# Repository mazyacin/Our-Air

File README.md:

<div align="center">
  
</div>
<div align="center">

</div>

<h1 align="center">Our-Air</h1>

<h2 align ="center">A platform for Our Environment:</h2> 

التلميذ : **مزوز أحمد الامين** 

**مسابقة الابتكار المدرسي الطبعة 2 الانظمة الذكية و انترنت الاشياء**

**هذا المشروع مفتوح المصدر تحت رخصة GNU  و هذه الجيت هاب ريبو نسخة احتياطية في حالة تلف ملفات المسابقة المرفقة** 
<h1 align="center"> 
The Problem :
</h1>

<h4 align="center"> With the overall all change with Our environment  we notice an increasing in Disasters like Air Pollution ,Wildfires
Water Pollution, Big Chemical Accidents, and environmental emergencies , but we only act when they happen , what if we 
had something , that lets us do advanced research and predicting</h4>

**Our-Air** Is a complete environmental scanning network that with the **flagship best in the world** sensors that scan for :

**Nitrogen Oxides(NOX)** : A group of very important gases because they are the same gases that cars and Factories emit 

**Volatile Organic Compounds (VOCs)** : A group of gases that is emitted from Paint, Oil Refineries, and Factories in general

**Humidity** : The consternation of vapor water in the Air , it is the Reason for Mold, and important for Respiratory Comfort 

**Temperature** : It tells us the thermal state of our environment, main reason of heatstroke

**Barometric Pressure** : It tells us the weight of the atmosphere, can be used to predict storms/rain

**Carbon Dioxide** : True sensing of the Co2 that`s  in the air we breath

**RunTime** : Nodes Up to 1.2 years of run time on 2x18650 in a parallel configuration, and Master around 87h of runtime on its backup battery 
with automatic Power Switching

---

And Our-Air has a **Desktop App** made to analyze the data both live and in a **sqlite db** format with **advanced environment researching tools** such as SQL query code field and professional graphs with a sleek design

<div align="center">

</div>

---
<h1 align="center"> 
But Why Our-Air : 
</h1>

-1 Its **fully open source**  , This project does`nt have to stop its development   

-2 The sensors all have 2 common reading and those are the humidity and temperature, and this lets us compare sensor data to detect faulty sensors 

-3 Community driven nodes that the  **smart** system adds to its **network**  

-4 Achieving **Long Range** without a Lora IC, our system uses a broadcasting esp-now interface with range up to 1.5km 

-5 No encryption to the sent packets  and broadcast mode, this lets solo researchers and tech hobbyists check their local environment data , even build their own project around the sensor data

-6 Very versatile the system is dynamic so it can read multiple kinds of data , For example someone can make one that watches water level at a nearby lake,

Or someone can make a bracelet with a button to notify the nearby receiver when that the person wearing the bracelet is lost, 

<h1 align="center"> 
Our-Air Node technical details 
</h1>

<h2 align="center"> 
Schematic : 
</h2>

<div align="center">
  
</div>

<h1 align="center"> 
Rough Bom : 
</h1>

 **Microcontroller : Esp32 C3 U1 N4 , Risc-V 160Mhz , 4MB of flash memory** 

<h2 align="center"> 
Sensors: 
</h2>

   | Sensor| Manufacturer | Description |
| --- | --- | --- |
| Bme690 | Bosch | The bme690 is Bosch latest environment sensor , and is the worlds best general environmental sensor , it is set to Spi Mode |
| SGP41| Senisiron|one of Senisiron`s latest Sensors whats special about it is its NOX sensing|
| SCD41| Senisiron|one of the Only sensors in the World , that can truly sense CO2 in the Air| 

<h2 align="center"> 
ICs: 
</h2>

   | Ic| Manufacturer | Description |
| --- | --- | --- |
| IP2312 | Injoinic | a high end charging ic set to 3A charging, whats special about it is the buck based design allowing low heat under full load |
| TPS63802| Texas instruments  |a high efficiency Buck and Boost ic with a Input voltage of 1.2v to 5.5v and Output of 3.3v , its efficiency is 95% , at full load it reaches 45°C which prevents burnouts, and its design lets use an 18650 directly , in the pcb its  used to power the components|
| CK340k| WCH |its a USB to UART programmer, in this case its used to flash the code to the MCU , and view live data , also offering debugging for both Nodes and Master| 

<div align="center">
  
</div>
<h2 align="center"> 
Pcb Specs :
</h2>

 **4 Layer Design** : a 4 layer based pcb design lets us minimize Emi Noise , Improve Stability and Reliability
 
 **TearDrops** : they Improve Reliability on the Long Run , its a must for a pcb like this that runs for long sessions
 
 **Smart heat accommodated design** : the Sensors are sensitive to heat so i designed it for thermal isolation 
 
 **Stitching Vias** : they were used to lower noise and help with heating 

 **fencing Vias** : they are used to make sure the LongRange Stays stable
 
 **External Antenna** : there is a IPX connector to connect an external Antenna

<div align="center">
  
</div>
<h1 align="center"> 
Casing Design : 
</h1>

  <h2 align="center"> 
Features : 
</h2>

   **OuterWalls** : ~125mm x 98mm 
      
   **InnerWalls** : ~120mm x 95mm
     
  **Wall Thickness** : 3mm
      
   **Closing Mechanism** : Annular snap-fit with 2mm long lip and 2 vertical cuts  for easier use when closing or opening
      
   **Meterial** : 9600 White Resin
      
   **Breathing Vents** : needed so the sensors can read the measurement of outside air
   
   **Ports** : there are spaces for the 2 USB C receptacles (35mm x ~4mm)and the external antenna(~7mm x ~15mm)

   <h1 align="center"> 
Our-Air Master technical details 
</h1>

<h2 align="center"> 
Schematic : 
</h2>

<div align="center">
  
</div>

<h1 align="center"> 
Rough Bom : 
</h1>

 **Microcontroller : Esp32 C3 U1 N4 , Risc-V 160Mhz , 4MB of flash memory** 
 **SD Card (8gb)

ICs: 
</h2>

   | Ic| Manufacturer | Description |
| --- | --- | --- |
| IP2312 | Injoinic | a high end charging ic set to 3A charging, whats special about it is the buck based design allowing low heat under full load |
| TPS63802| Texas instruments  |a high efficiency Buck and Boost ic with a Input voltage of 1.2v to 5.5v and Output of 3.3v , its efficiency is 95% , at full load it reaches 45°C which prevents burnouts, and its design lets use an 18650 directly , in the pcb its  used to power the components|
| CK340k| WCH |its a USB to UART programmer, in this case its used to flash the code to the MCU , and view live data , also offering debugging for both Nodes and Master| 
| DS3231SN| Maxim Integrated |A RTC Ic (Real Time Clock ic ) used to make the timestamps of the when Sensors is received by the Master  | 
<div align="center">
  
</div>
<h2 align="center"> 
Pcb Specs :
</h2>

 **4 Layer Design** : a 4 layer based pcb design lets us minimize Emi Noise , Improve Stability and Reliability
 
 **TearDrops** : they Improve Reliability on the Long Run , its a must for a pcb like this that runs for long sessions
 
 **Stitching Vias** : they were used to lower noise and help with heating 

 **fencing Vias** : they are used to make sure the LongRange Stays stable
 
 **External Antenna** : there is a IPX connector to connect an external Antenna

<div align="center">
  
</div>
<h1 align="center"> 
Casing Design : 
</h1>

  <h2 align="center"> 
Features : 
</h2>

   **OuterWalls** : ~168mm x 107mm 
      
   **InnerWalls** : ~160mm x 100mm
     
  **Wall Thickness** : 3mm
      
   **Closing Mechanism** : Annular snap-fit with 2mm long lip and 2 vertical cuts  for easier use when closing or opening
      
   **Meterial** : 9600 White Resin
   
   **Ports** : there are spaces for the 2 USB C receptacles (35mm x ~4mm)and the external antenna(~7mm x ~15mm) and Sd card ( ~60mm x 16mm) the holes for the sd card and external antenna are merged

<h1 align="center">
Node Logic  :
</h1>

<h3 >
An Our-Air node can last up to a whole year thanks to deepsleep and low power sensors and the explanation of the logic is as of the following:

 Deepsleep and Lightsleep timers are 15 minutes for the Deepsleep and 10 seconds for the Lightsleep

after waking up from deepsleep 

it checked for the reason of waking up this allows us to use the debugger with the nodes where when rx is low the rtc wakes up the  mcu,if the reason is the timer ended it initiates the sensors then goes to light sleep 

after light sleep it reads the sensors and makes a json packet then sends it with espnow set to broadcast mode and long range on and the send strength to 80(max)

it sends 3 times to prevent data loss 
then goes back to sleep

it had an average power consumption of 1.1mAh per hour

</h3>
<h1 align="center">
Master Logic  :
</h1>

<h3>
The Master can last almost 3 days on its backup battery,with automatic power switching from main source to backup and the explanation of the logic is as of the following:

the Master actively scans for espnow packets in Lr mode (Long Range) and deserialises it with json 

then checks if its mac address is in the blacklist

if yes it ignores the packet

if no it parses and adds a time stamp using the rtc ic it into a queue then a function that writes it into an Entity Attributed Value sqlite database on an sd card 
</h3>
<div align="center">
   
</div>

<h1>
The Database viewer App :
</h1>

<h2>
It has 2 Parts :
</h2>

<h3>
-1 A tool that turns the database into Graphs to detect spikes it has 2 buttons one to select location and the other to select reading type (what reading you want to graph) then it makes a graph with zoom in and out and a slider to be able to see all of the graph 

-2 An SQL manual query code box for advanced research with a console to show errors and output then a table to see the query result 

right now it is limited to 300 rows max
</h3>
<h1>
The Live viewer App :
</h1>

<h2>
It has 3 Parts :
</h2>

<h3>
-1 A box shows live readings taken from the master through USB and updates automatically, also there is a button to select a usb port

-2 it is used to flash location and blacklist into the master and node,it automatically detectes if the plugged in is thr master or node,

if master is connected you get a text field to write MAC address of a node you want to blacklist to sent you click enter 

also there is a reflash blacklist, the app saves a copy of thr blacklist and if the master lost its blacklist you can reflash it whole

if node is connected you get a textfield
you write in the location you want to flash to the node to assign a location to it and it shows up in the database 
 
-3 a debug table that helps with debugging a broken node or master that shows debug prints 
</h3>
<h1 align ="center">
  Installing the Apps :
</h1>
<div align="center">
  
</div>
<h2>
  To install the Apps you Have 2 Options : 
</h2>
<h3>
  -1 Directly download the .exe from the Release "Desktop Apps executables" (the Apps have only been tested on windows 10 )
  
   and put the shortcut on your desktop , if the shortcut doesnt show the App Icon, right click it and select "properties" then "change 
   
   icon"then "browse" then select the .ico file found in the folder of the app
  
  -2 From the source Files , you can download them in the "Apps Code" folder or you can download the Release "Flutter OpenSource Files" 
  
   after you install them you put them in you put them in a flutter project folder , and you run "flutter pub get " and then you can 
   
   compile or run it through the IDE (you need visual studio 2022 with "Desktop development with C++" workload installed )
</h3>
<div align="center">

</div>
<h1 align="center">
Flashing The Software
</h1>

Master / Node: 
**Flashing the Software is The Same For The Node or Master**  :  

 **-1** Make sure you Have ch340x drivers installed (or Arduino ide since it comes packaged with It)
 
 **-2** Download the .ino Sketches 
 
 **-3** Make Sure you have these libraries installed : 
 
  **For the Master .ino**: 
  
<SPI.h>,<WiFi.h>,<esp_now.h>
<Wire.h>, <sqlite3.h>,<FS.h>
<SD.h>,<RTClib.h> ,<ArduinoJson.h>
<queue>,<esp_wifi.h>,<vector>

 **For the Node .ino** : 
 
<Wire.h>, <7semi_BME690.h>, <Adafruit_SGP41.h>
<SensirionI2cScd4x.h>, <SPI.h>, <WiFi.h>
<esp_now.h>, <ArduinoJson.h>, <esp_wifi.h>

 **-4** Open Arduino Ide (platformIo and esp-idf are not supported) and load the .ino , in the "**file**" button

 **-5** plug in Node/Master through the top usb c port (lower ones are for 3A charging only )

 **-6** select the Node/Master from the COM selection button at the top 

 **-7** Click Upload ( this might Take Some time)

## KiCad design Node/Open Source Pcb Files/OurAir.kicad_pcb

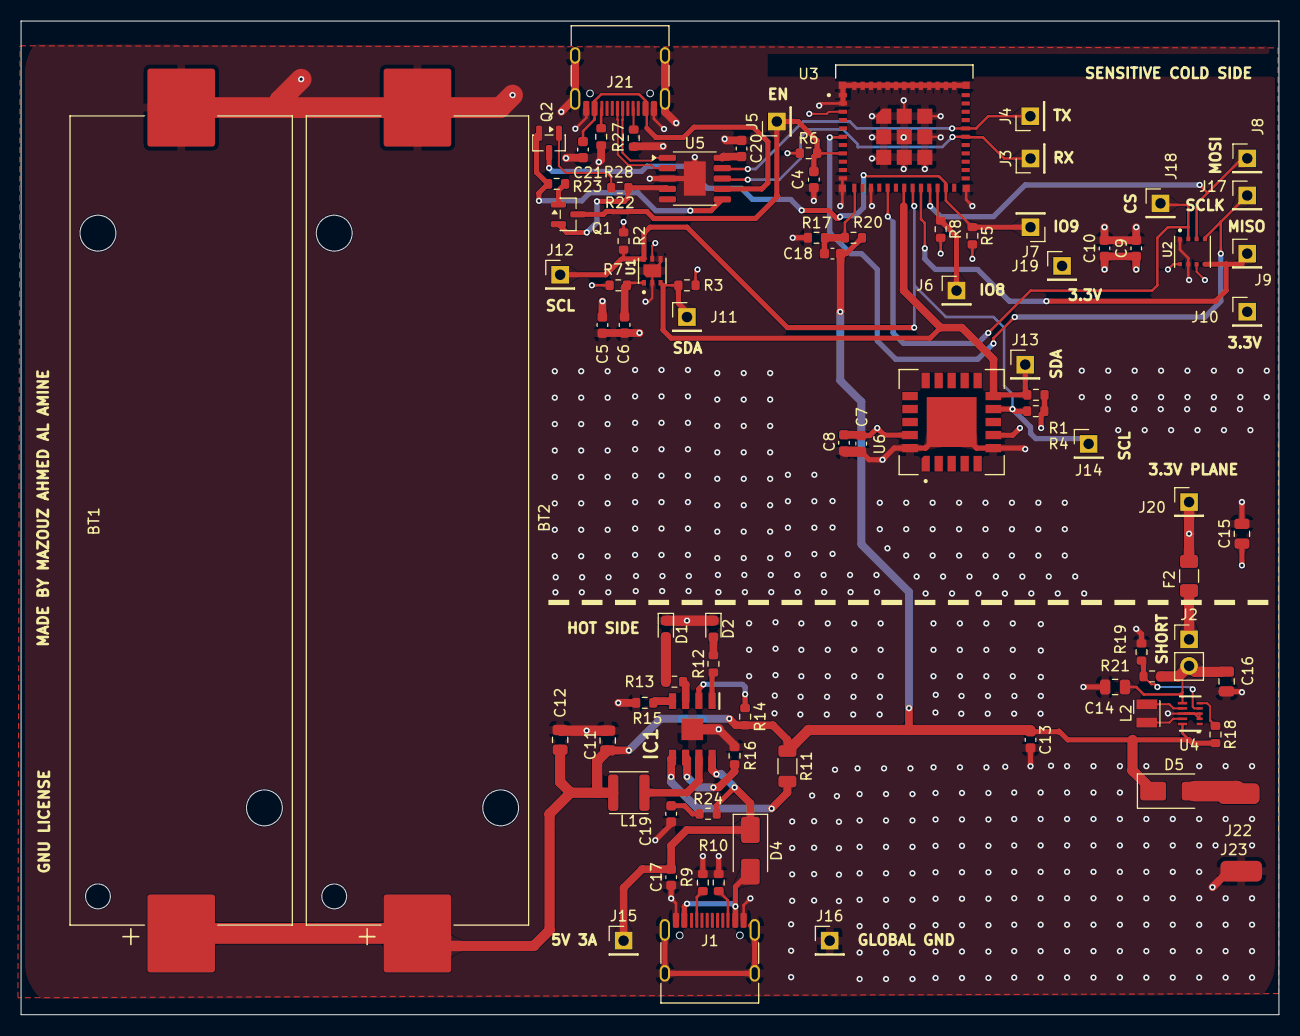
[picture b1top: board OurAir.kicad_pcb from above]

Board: 4 copper layers, 120.9 x 95.5 mm, 85 parts (0 on the bottom side), 47 nets.

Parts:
BT1, BT2: Battery; BatteryHolder_Keystone_1042_1x18650
C4, C6, C8, C9, C10, C18, C20, C21: 0.1uf 16v; C_0603_1608Metric
C5, C7, C17: 1uf 16v; C_0603_1608Metric
C11, C12, C14, C15, C16: 22uf 16v; C_0805_2012Metric
C13, C19: 10uf; C_0603_1608Metric
D1, D2: LED; LED_0603_1608Metric
D4, D5: SS34; D_SMA
F2: Fuse; Fuse_1206_3216Metric
IC1: IP2312; SOIC127P600X165-9N
J1, J21: USB_C_Receptacle_USB2.0_16P; USB_C_Receptacle_HRO_TYPE-C-31-M-12
J2: Conn_01x02_Pin; PinHeader_1x02_P2.54mm_Vertical
J3, J4, J5, J6, J7, J8, J9, J10, J11, J12, J13, J14, J15, J16, J17, J18, J19, J20: Conn_01x01_Pin; PinHeader_1x01_P2.54mm_Vertical
J22, J23: Conn_01x01_Pin; SolderWirePad_1x01_SMD_2x4mm
L1: 1uH; L_Wuerth_PMFI-353220
L2: 0.47uH; L_Wurth_WE-LQSH-2512
Q1, Q2: SS8050; SOT-23
R1, R2, R3, R4: 2.2k Ohm; R_0603_1608Metric
R5, R6, R8, R22, R23: 10k Ohm; R_0603_1608Metric
R7: 4.7 Ohm; R_0603_1608Metric
R9, R10, R27, R28: 5.1k Ohm; R_0603_1608Metric
R11: 0.5 Ohm; R_1206_3216Metric
R12, R13: 100 Ohm; R_0603_1608Metric
R14: 1k Ohm; R_0603_1608Metric
R15, R17, R20: 51k Ohm; R_0603_1608Metric
R16: 47k Ohm; R_0603_1608Metric
R18: 100k Ohm; R_0603_1608Metric
R19: 91k Ohm; R_0603_1608Metric
R21: 511k Ohm; R_0603_1608Metric
R24: 2 Ohm; R_0603_1608Metric
U1: SGP41-D-R4; XDCR_SGP41-D-R4
U2: BME688; IC_BME688
U3: ESP32-C3-MINI-1U-N4; XCVR_ESP32-C3-MINI-1U-N4
U4: TPS63802DLAT; DLA0010A
U5: CH340K; SSOP-10-1EP_3.9x4.9mm_P1mm_EP2.1x3.3mm
U6: SCD41-D-R2; XDCR_SCD41-D-R2

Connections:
5V: C21.2, J21.A4 (VBUS), J21.A9 (VBUS), J21.B4 (VBUS), J21.B9 (VBUS), U5.7 (VCC)
D+: J21.A6 (D+), U5.1 (UD+)
D-: J21.A7 (D-), U5.2 (UD-)
DTR: C4.1, J5.1 (Pin_1_1), Q1.3 (C), R6.2, U3.8 (EN)
GND: BT1.2 (-), BT2.2 (-), C4.2, C5.1, C6.1, C7.2, C8.2, C9.2, C10.2, C11.2, C12.2, C13.2, C14.1, C15.2, C16.1, C17.1, C19.1, C20.1, C21.1, D1.1 (K), D2.1 (K), IC1.9 (GND), J1.A1 (GND), J1.A12 (GND), J1.B1 (GND), J1.B12 (GND), J1.SH (SHIELD), J16.1 (Pin_1_1), J21.A1 (GND), J21.A12 (GND), J21.B1 (GND), J21.B12 (GND), J21.SH (SHIELD), J23.1 (Pin_1_1), R9.2, R10.2, R15.2, R16.2, R17.1, R19.2, R27.2, R28.2, U1.2 (VSS), U1.4 (N/A), U1.7 (EXP), U2.1 (GND), U2.7 (GND), U3.1 (GND), U3.2 (GND), U3.11 (GND), U3.14 (GND), U3.36 (GND), U3.37 (GND), U3.38 (GND), U3.39 (GND), U3.40 (GND), U3.41 (GND), U3.42 (GND), U3.43 (GND), U3.44 (GND), U3.45 (GND), U3.46 (GND), U3.47 (GND), U3.48 (GND), U3.49_1 (GND), U3.49_2 (GND), U3.49_3 (GND), U3.49_4 (GND), U3.49_5 (GND), U3.49_6 (GND), U3.49_7 (GND), U3.49_8 (GND), U3.49_9 (GND), U3.50 (GND), U3.51 (GND), U3.52 (GND), U3.53 (GND), U4.2 (MODE), U4.3 (AGND), U4.8 (GND), U5.3 (GND), U5.11 (GND), U6.6 (GND), U6.20 (GND), U6.21 (GND)
unnamed: C19.2, R24.1
unnamed: D1.2 (A), R13.2
unnamed: D2.2 (A), R12.2
unnamed: D4.2 (A), J1.A4 (VBUS), J1.A9 (VBUS), J1.B4 (VBUS), J1.B9 (VBUS)
unnamed: C17.2, D4.1 (K), IC1.8 (VIN), J15.1 (Pin_1_1), R24.2
unnamed: D5.2 (A), J22.1 (Pin_1_1)
unnamed: IC1.5 (BAT), R11.2
unnamed: IC1.1 (D1), R12.1
unnamed: IC1.3 (D2), R13.1
unnamed: IC1.6 (ICHG), R16.1
unnamed: IC1.4 (NTC), R15.1
unnamed: IC1.7 (SW), L1.1
unnamed: IC1.2 (TEST), R14.1
unnamed: J1.A5 (CC1), R9.1
unnamed: J1.B5 (CC2), R10.1
unnamed: F2.1, J2.1
unnamed: C14.2, C16.2, J2.2, R21.1, U4.6 (VOUT)
unnamed: J6.1 (Pin_1_1), R8.1, U3.22 (IO8)
unnamed: J8.1 (Pin_1_1), U2.3 (SDI), U3.21 (IO7)
unnamed: J9.1 (Pin_1_1), U2.5 (SDO), U3.20 (IO6)
unnamed: C5.2, C7.1, C8.1, C9.1, C10.1, C15.1, F2.2, J10.1 (Pin_1_1), J19.1 (Pin_1_1), J20.1 (Pin_1_1), R1.1, R2.1, R3.1, R4.1, R5.2, R6.1, R7.1, R8.2, U1.5 (VDDH), U2.6 (VDDIO), U2.8 (VDD), U3.3 (3V3), U6.7 (VDD), U6.19 (VDDH)
unnamed: J11.1 (Pin_1_1), J13.1 (Pin_1_1), R3.2, R4.2, U1.3 (SDA), U3.18 (IO4), U6.10 (SDA)
unnamed: J12.1 (Pin_1_1), J14.1 (Pin_1_1), R1.2, R2.2, U1.6 (SCL), U3.19 (IO5), U6.9 (SCL)
unnamed: J17.1 (Pin_1_1), U2.4 (SCK), U3.6 (IO3)
unnamed: J18.1 (Pin_1_1), U2.2 (CSB), U3.16 (IO10)
unnamed: J21.A5 (CC1), R27.1
unnamed: J21.B5 (CC2), R28.1
unnamed: Q1.1 (B), R23.2
unnamed: Q1.2 (E), R22.1, U5.4 (~DTR)
unnamed: Q2.1 (B), R22.2
unnamed: Q2.2 (E), R23.1, U5.6 (~RTS)
unnamed: C6.2, R7.2, U1.1 (VDD)
unnamed: C18.1, R17.2, R20.1, U3.12 (IO0)
unnamed: R19.1, R21.2, U4.4 (FB)
unnamed: L2.1, U4.9 (L1)
unnamed: L2.2, U4.7 (L2)
unnamed: R18.1, U4.5 (PG)
unnamed: C20.2, U5.10 (V3)
RTS: J7.1 (Pin_1_1), Q2.3 (C), R5.1, U3.23 (IO9)
RX: J4.1 (Pin_1_1), U3.31 (TXD0), U5.9 (RXD)
TX: J3.1 (Pin_1_1), U3.30 (RXD0), U5.8 (TXD)
Vin: BT1.1 (+), BT2.1 (+), C11.1, C12.1, C13.1, C18.2, D5.1 (K), L1.2, R11.1, R14.2, R18.2, R20.2, U4.10 (VIN)

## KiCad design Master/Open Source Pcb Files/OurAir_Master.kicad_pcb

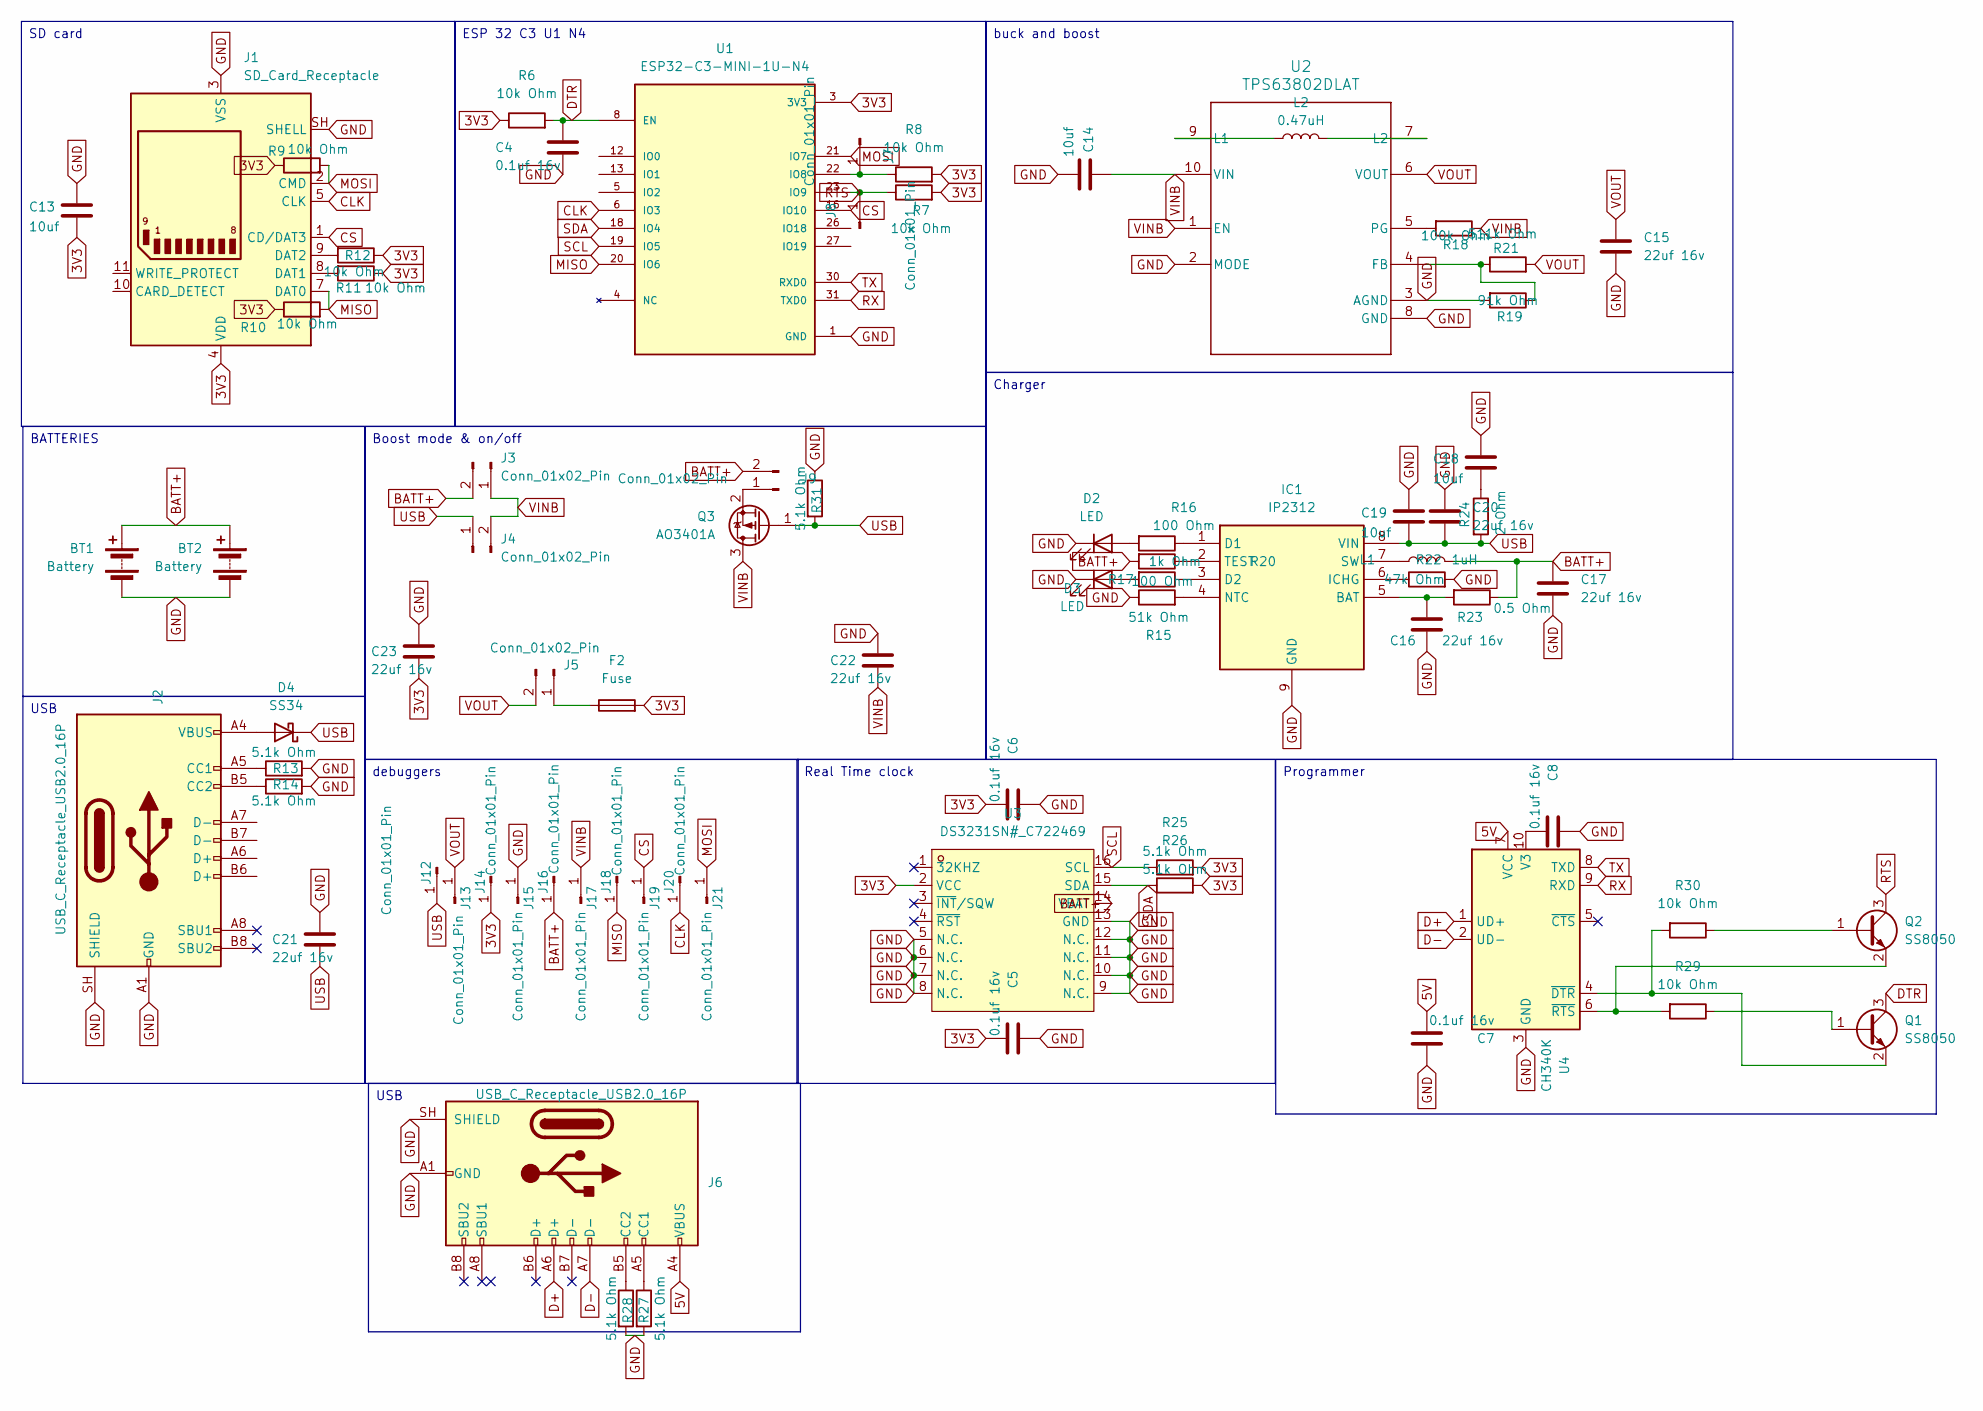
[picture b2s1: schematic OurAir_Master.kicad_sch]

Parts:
BT1, BT2: Battery; BatteryHolder_Keystone_1042_1x18650; LCSC C5249310
C4, C5, C6, C7, C8: 0.1uf 16v; C_0603_1608Metric; LCSC C14663
C13, C14, C18, C19: 10uf; C_0603_1608Metric; LCSC C96446
C15, C16, C17, C20, C21, C22, C23: 22uf 16v; C_0805_2012Metric; LCSC C45783
D2, D3: LED; LED_0603_1608Metric; LCSC C2286
D4: SS34; D_SMA; LCSC C8678
F2: Fuse; Fuse_1206_3216Metric; LCSC C883128
IC1: IP2312; SOIC127P600X165-9N; Manufacturer_Part_Number IP2312; LCSC C605433
J1: SD_Card_Receptacle; SD-SMD_SD-006M; LCSC C125615
J2, J6: USB_C_Receptacle_USB2.0_16P; USB_C_Receptacle_HRO_TYPE-C-31-M-12; LCSC C165948
J3, J4, J5, J9: Conn_01x02_Pin; PinHeader_1x02_P2.54mm_Vertical; LCSC C124375
J7, J8, J12, J13, J14, J15, J16, J17, J18, J19, J20, J21: Conn_01x01_Pin; PinHeader_1x01_P2.54mm_Vertical; LCSC C81276
L1: 1uH; L_Wuerth_PMFI-353220; LCSC C3002565
L2: 0.47uH; L_Wurth_WE-LQSH-2512; LCSC C5441998
Q1, Q2: SS8050; SOT-23; LCSC C2150
Q3: AO3401A; SOT-23; LCSC C15127
R6, R7, R8, R9, R10, R11, R12, R29, R30: 10k Ohm; R_0603_1608Metric; LCSC C25804
R13, R14, R25, R26, R27, R28, R31: 5.1k Ohm; R_0603_1608Metric; LCSC C23186
R15: 51k Ohm; R_0603_1608Metric; LCSC C23196
R16, R17: 100 Ohm; R_0603_1608Metric; LCSC C22775
R18: 100k Ohm; R_0603_1608Metric; LCSC C25803
R19: 91k Ohm; R_0603_1608Metric; LCSC C325723
R20: 1k Ohm; R_0603_1608Metric; LCSC C21190
R21: 511k Ohm; R_0603_1608Metric; LCSC C23194
R22: 47k Ohm; R_0603_1608Metric; LCSC C25819
R23: 0.5 Ohm; R_1206_3216Metric; LCSC C25340
R24: 2 Ohm; R_0603_1608Metric; LCSC C22977
U1: ESP32-C3-MINI-1U-N4; XCVR_ESP32-C3-MINI-1U-N4; PARTREV v1.0; LCSC C2911374
U2: TPS63802DLAT; DLA0010A; LCSC C1849531
U3: DS3231SN#_C722469; SOIC-16_L10.3-W7.5-P1.27-LS10.3-BL; LCSC Part C722469
U4: CH340K; SSOP-10-1EP_3.9x4.9mm_P1mm_EP2.1x3.3mm; LCSC C968586

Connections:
3V3: C5.2, C6.2, C13.2, C23.2, F2.2, J1.4 (VDD), J14.1 (Pin_1_1), R6.1, R7.2, R8.2, R9.1, R10.1, R11.1, R12.1, R25.2, R26.2, U1.3 (3V3), U3.2 (VCC)
5V: C7.2, J6.A4 (VBUS), J6.A9 (VBUS), J6.B4 (VBUS), J6.B9 (VBUS), U4.7 (VCC)
BATT+: BT1.1 (+), BT2.1 (+), C17.1, J3.2, J9.2, J16.1 (Pin_1_1), L1.2, R20.2, R23.1, U3.14 (VBAT)
CLK: J1.5 (CLK), J20.1 (Pin_1_1), U1.6 (IO3)
CS: J1.1 (CD/DAT3), J19.1 (Pin_1_1), U1.16 (IO10)
D+: J6.A6 (D+), U4.1 (UD+)
D-: J6.A7 (D-), U4.2 (UD-)
DTR: C4.1, Q1.3 (C), R6.2, U1.8 (EN)
GND: BT1.2 (-), BT2.2 (-), C4.2, C5.1, C6.1, C7.1, C8.1, C13.1, C14.2, C15.2, C16.2, C17.2, C18.1, C19.1, C20.1, C21.1, C22.1, C23.1, D2.1 (K), D3.1 (K), IC1.9 (GND), J1.3 (VSS), J1.6 (VSS), J1.SH (SHELL), J2.A1 (GND), J2.A12 (GND), J2.B1 (GND), J2.B12 (GND), J2.SH (SHIELD), J6.A1 (GND), J6.A12 (GND), J6.B1 (GND), J6.B12 (GND), J6.SH (SHIELD), J15.1 (Pin_1_1), R13.2, R14.2, R15.1, R19.2, R22.2, R27.2, R28.2, R31.1, U1.1 (GND), U1.2 (GND), U1.11 (GND), U1.14 (GND), U1.36 (GND), U1.37 (GND), U1.38 (GND), U1.39 (GND), U1.40 (GND), U1.41 (GND), U1.42 (GND), U1.43 (GND), U1.44 (GND), U1.45 (GND), U1.46 (GND), U1.47 (GND), U1.48 (GND), U1.49_1 (GND), U1.49_2 (GND), U1.49_3 (GND), U1.49_4 (GND), U1.49_5 (GND), U1.49_6 (GND), U1.49_7 (GND), U1.49_8 (GND), U1.49_9 (GND), U1.50 (GND), U1.51 (GND), U1.52 (GND), U1.53 (GND), U2.2 (MODE), U2.3 (AGND), U2.8 (GND), U3.5 (N.C.), U3.6 (N.C.), U3.7 (N.C.), U3.8 (N.C.), U3.9 (N.C.), U3.10 (N.C.), U3.11 (N.C.), U3.12 (N.C.), U3.13 (GND), U4.3 (GND), U4.11 (GND)
MISO: J1.7 (DAT0), J18.1 (Pin_1_1), R10.2, U1.20 (IO6)
MOSI: J1.2 (CMD), J21.1 (Pin_1_1), R9.2, U1.21 (IO7)
unnamed: C18.2, R24.1
unnamed: D2.2 (A), R16.2
unnamed: D3.2 (A), R17.2
unnamed: D4.2 (A), J2.A4 (VBUS), J2.A9 (VBUS), J2.B4 (VBUS), J2.B9 (VBUS)
unnamed: C16.1, IC1.5 (BAT), R23.2
unnamed: IC1.1 (D1), R16.1
unnamed: IC1.3 (D2), R17.1
unnamed: IC1.6 (ICHG), R22.1
unnamed: IC1.4 (NTC), R15.2
unnamed: IC1.7 (SW), L1.1
unnamed: IC1.2 (TEST), R20.1
unnamed: J1.8 (DAT1), R11.2
unnamed: J1.9 (DAT2), R12.2
unnamed: J2.A5 (CC1), R13.1
unnamed: J2.B5 (CC2), R14.1
unnamed: F2.1, J5.1
unnamed: J6.A5 (CC1), R27.1
unnamed: J6.B5 (CC2), R28.1
unnamed: J7.1 (Pin_1_1), R8.1, U1.22 (IO8)
unnamed: J9.1, Q3.2 (S)
unnamed: Q1.1 (B), R29.1
unnamed: Q1.2 (E), R30.2, U4.4 (~DTR)
unnamed: Q2.1 (B), R30.1
unnamed: Q2.2 (E), R29.2, U4.6 (~RTS)
unnamed: R19.1, R21.1, U2.4 (FB)
unnamed: L2.1, U2.9 (L1)
unnamed: L2.2, U2.7 (L2)
unnamed: R18.2, U2.5 (PG)
unnamed: C8.2, U4.10 (V3)
RTS: J8.1 (Pin_1_1), Q2.3 (C), R7.1, U1.23 (IO9)
RX: U1.31 (TXD0), U4.9 (RXD)
SCL: R25.1, U1.19 (IO5), U3.16 (SCL)
SDA: R26.1, U1.18 (IO4), U3.15 (SDA)
TX: U1.30 (RXD0), U4.8 (TXD)
USB: C19.2, C20.2, C21.2, D4.1 (K), IC1.8 (VIN), J4.1, J12.1 (Pin_1_1), Q3.1 (G), R24.2, R31.2
VINB: C14.1, C22.2, J3.1, J4.2, J17.1 (Pin_1_1), Q3.3 (D), R18.1, U2.1 (EN), U2.10 (VIN)
VOUT: C15.1, J5.2, J13.1 (Pin_1_1), R21.2, U2.6 (VOUT)

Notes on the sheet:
USB
debuggers
SD card
Charger
BATTERIES
buck and boost
Real Time clock
Programmer
Boost mode & on/off
ESP 32 C3 U1 N4

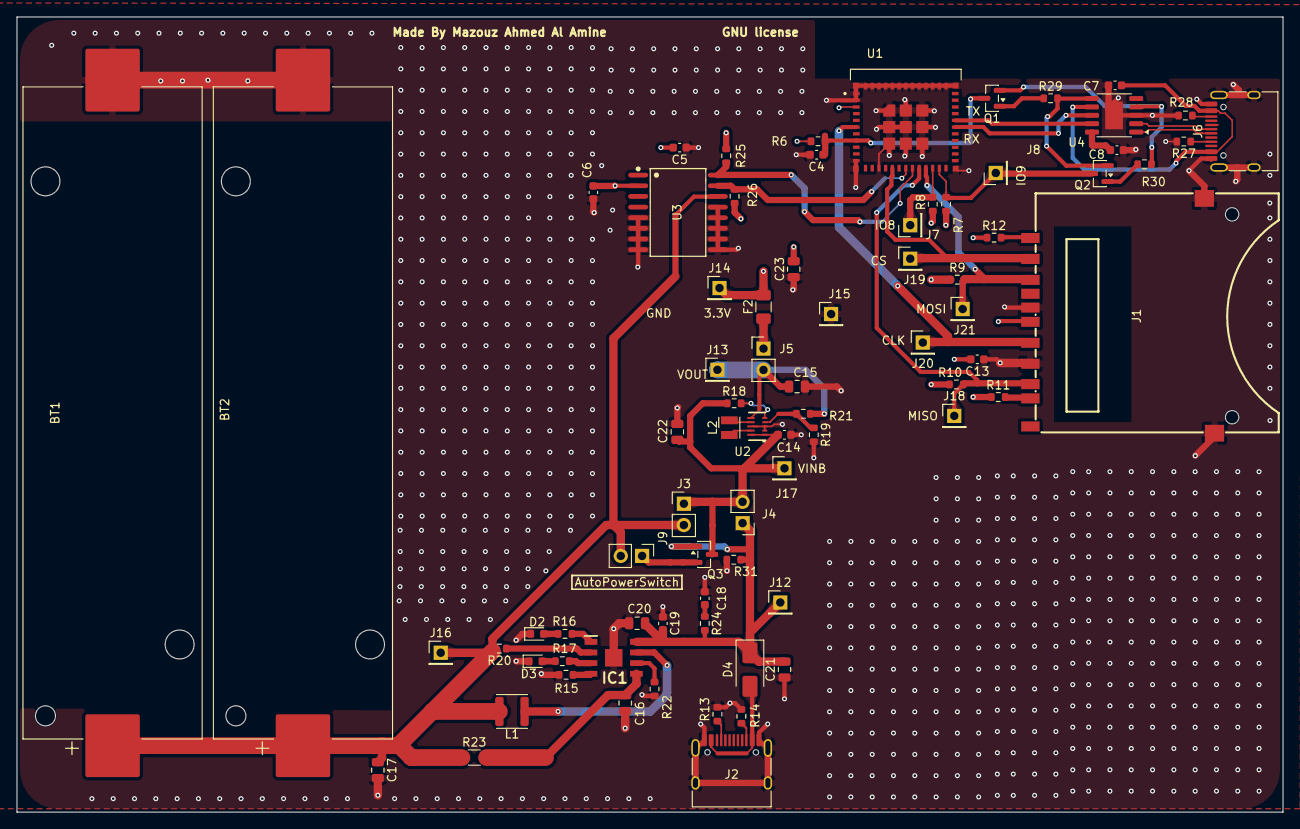
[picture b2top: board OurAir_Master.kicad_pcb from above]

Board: 4 copper layers, 151.0 x 94.8 mm, 77 parts (0 on the bottom side), 48 nets.
